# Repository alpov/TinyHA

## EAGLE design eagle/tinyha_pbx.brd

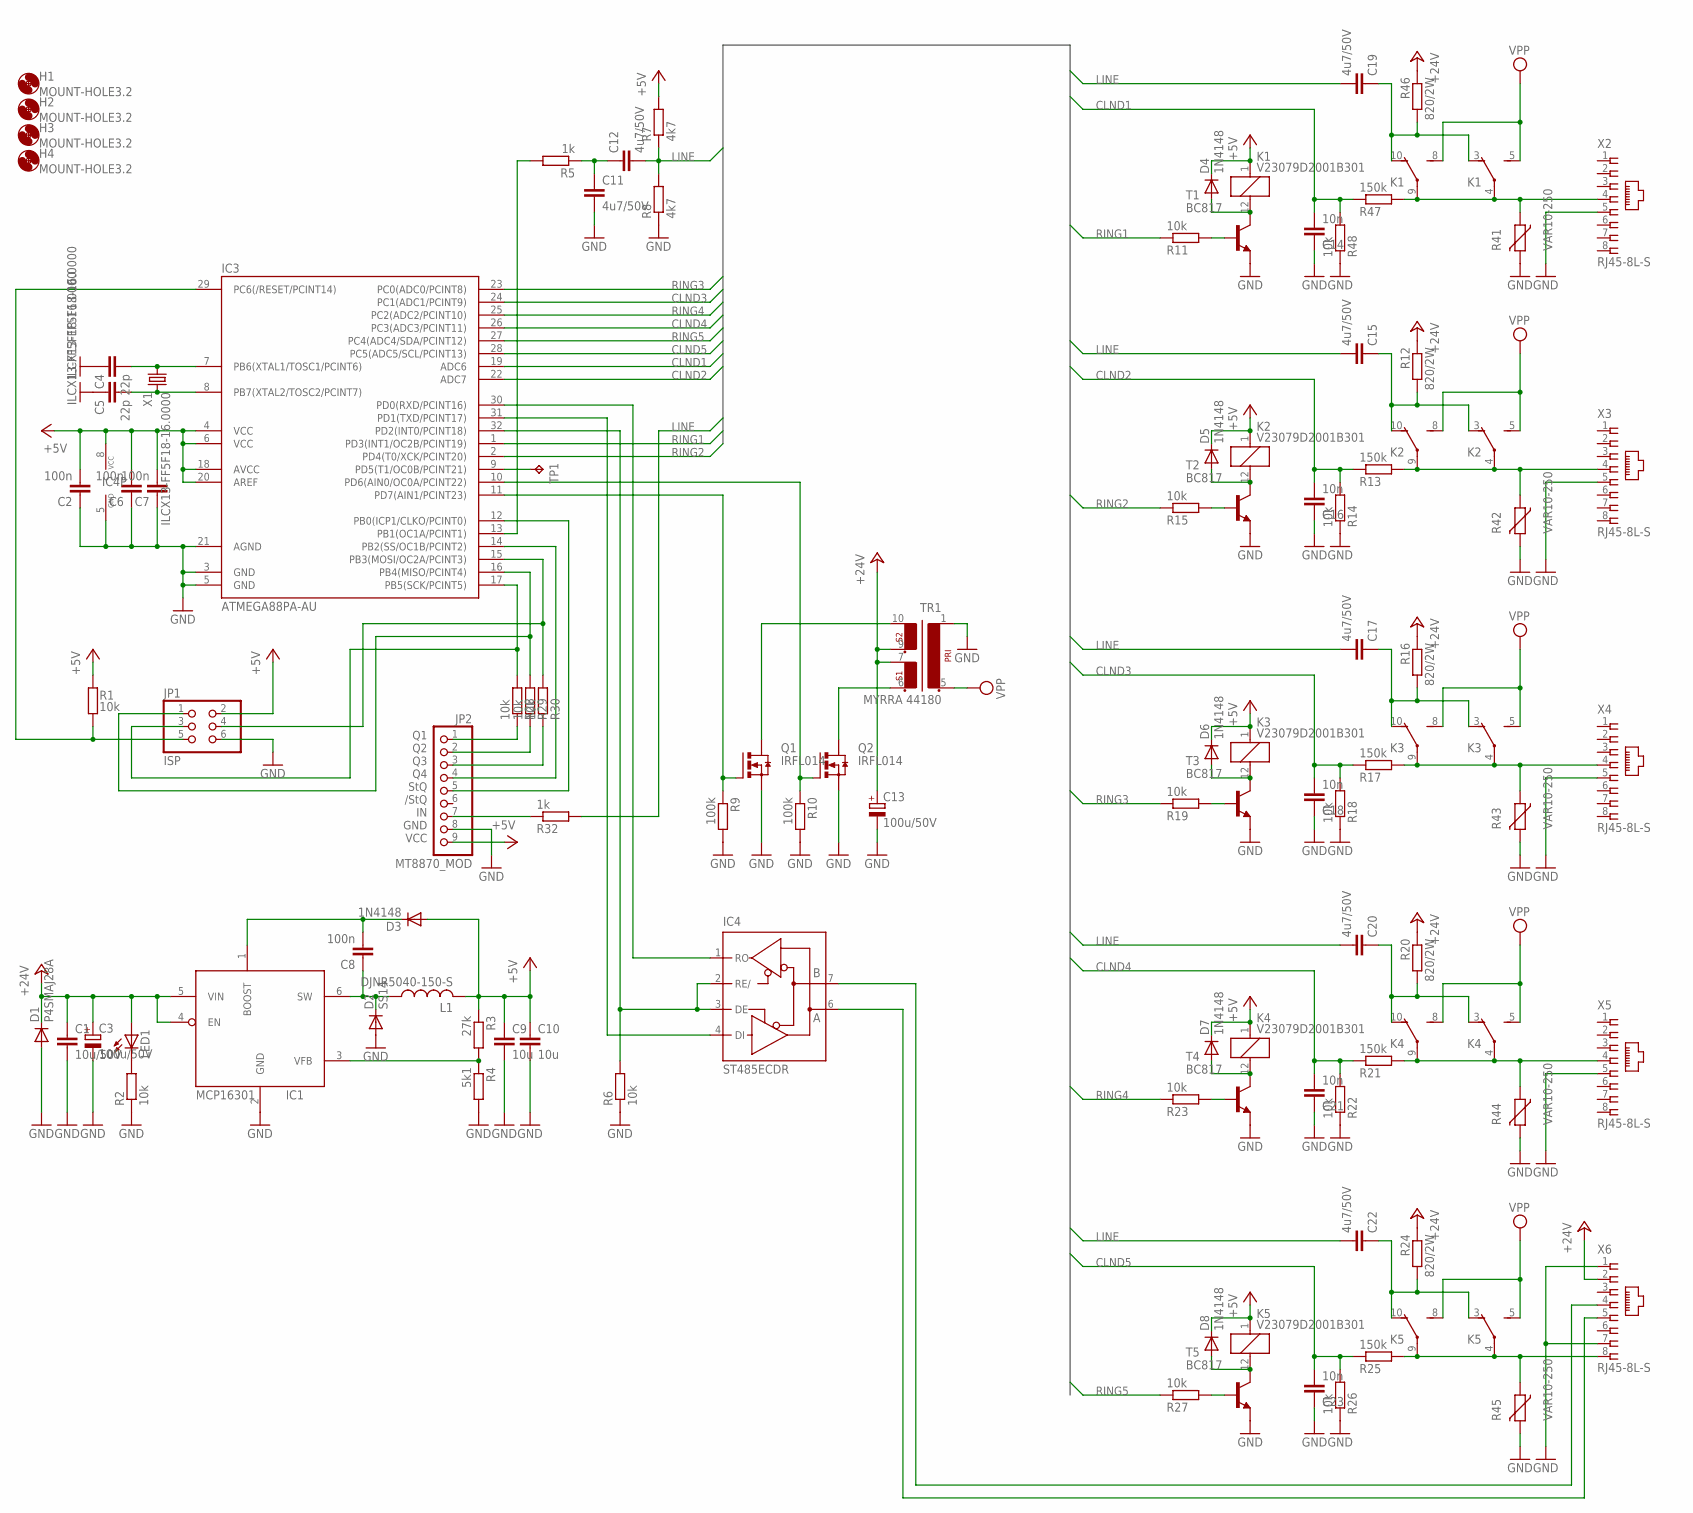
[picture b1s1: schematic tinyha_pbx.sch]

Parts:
C1: 10u/50V; C1210K
C2: 100n; C1206K
C3, C13: 100u/50V; E3,5-8
C4, C5: 22p; C0805K
C6, C7, C8: 100n; C0805K
C9, C10: 10u; C0805K
C11, C12, C15, C17, C19, C20, C22: 4u7/50V; C1206
C14, C16, C18, C21, C23: 10n; C1206
D1: P4SMAJ28A; DO214AC
D2: SS14; DO214AC
D3: 1N4148; MICROMELF-W
D4, D5, D6, D7, D8: 1N4148; MINIMELF
H1, H2, H3, H4: MOUNT-HOLE3.2; 3,2
IC1: MCP16301; SOT23-6L
IC3: ATMEGA88PA-AU; TQFP32-08
IC4: ST485ECDR; SO08
JP1: ISP; 2X03
JP2: MT8870_MOD; 1X09
K1, K2, K3, K4, K5: V23079D2001B301; V23079D
L1: DJNR5040-150-S; DJNR5040
LED1: LED3MM
Q1, Q2: IRFL014; SOT223
R1: 10k; R0805
R2, R6, R11, R14, R15, R18, R19, R22, R23, R26, R27, R28, R29, R30, R48: 10k; R1206
R3: 27k; R0805
R4: 5k1; R0805
R5, R32: 1k; R1206
R7, R8: 4k7; R1206
R9, R10: 100k; R1206
R12, R16, R20, R24, R46: 820/2W; 0411/15
R13, R17, R21, R25, R47: 150k; R1206
R41, R42, R43, R44, R45: VAR10-250; R-7,5
T1, T2, T3, T4, T5: BC817; SOT23-BEC
TP1: TPB2,54; B2,54
TR1: MYRRA 44180; EI30-2
X1: ILCX13-FF5F18-16.0000; SMD3225
X2, X3, X4, X5, X6: RJ45-8L-S; RJ45-NO-SHIELD

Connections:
+5V: C2.2, C6.2, C7.2, C9.1, C10.1, D3.A, D4.C, D5.C, D6.C, D7.C, D8.C, IC3.4 (VCC), IC3.6 (VCC), IC3.18 (AVCC), IC3.20 (AREF), IC4.8 (VCC), JP1.2, JP2.9, K1.1, K2.1, K3.1, K4.1, K5.1, L1.2, R1.1, R3.1, R7.2
+24V: C1.1, C3.+, C13.+, D1.C, IC1.4 (EN), IC1.5 (VIN), LED1.A, R12.1, R16.1, R20.1, R24.1, R46.1, TR1.7 (4), TR1.9 (5), X6.2
CLND1: C14.2, IC3.19 (ADC6), R47.1, R48.2
CLND2: C16.2, IC3.22 (ADC7), R13.1, R14.2
CLND3: C18.2, IC3.24 (PC1(ADC1/PCINT9)), R17.1, R18.2
CLND4: C21.2, IC3.26 (PC3(ADC3/PCINT11)), R21.1, R22.2
CLND5: C23.2, IC3.28 (PC5(ADC5/SCL/PCINT13)), R25.1, R26.2
DIR: IC3.32 (PD2(INT0/PCINT18)), IC4.2 (RE/), IC4.3 (DE), R6.2
GND: C1.2, C2.1, C3.-, C4.1, C5.1, C6.1, C7.1, C9.2, C10.2, C11.2, C13.-, C14.1, C16.1, C18.1, C21.1, C23.1, D1.A, D2.A, IC1.2 (GND), IC3.3 (GND), IC3.5 (GND), IC3.21 (AGND), IC4.5 (GND), JP1.6, JP2.8, Q1.3 (S), Q2.3 (S), R2.1, R4.2, R6.1, R8.1, R9.2, R10.2, R14.1, R18.1, R22.1, R26.1, R41.2, R42.2, R43.2, R44.2, R45.2, R48.1, T1.E, T2.E, T3.E, T4.E, T5.E, TR1.1, X1.2 (GND), X1.4 (GND), X2.5, X3.5, X4.5, X5.5, X6.1, X6.7
LINE: C12.2, C15.2, C17.2, C19.2, C20.2, C22.2, R7.1, R8.2, R32.2
MISO: IC3.16 (PB4(MISO/PCINT4)), JP1.1, R29.2
MOSI: IC3.15 (PB3(MOSI/OC2A/PCINT3)), JP1.4, R30.2
unnamed: D4.A, K1.12 (2), T1.C
unnamed: R11.2, T1.B
unnamed: JP2.1, R28.1
unnamed: C15.1, K2.3 (O), K2.10 (O), R12.2
unnamed: K3.4, K3.9, R17.2, R43.1, X4.4
unnamed: K5.4, K5.9, R25.2, R45.1, X6.8
unnamed: K2.4, K2.9, R13.2, R42.1, X3.4
unnamed: K4.4, K4.9, R21.2, R44.1, X5.4
unnamed: IC3.9 (PD5(T1/OC0B/PCINT21)), TP1.TP
unnamed: D5.A, K2.12 (2), T2.C
unnamed: R15.2, T2.B
unnamed: C17.1, K3.3 (O), K3.10 (O), R16.2
unnamed: JP2.7, R32.1
unnamed: D6.A, K3.12 (2), T3.C
unnamed: R19.2, T3.B
unnamed: C20.1, K4.3 (O), K4.10 (O), R20.2
unnamed: D7.A, K4.12 (2), T4.C
unnamed: LED1.K (C), R2.2
unnamed: R23.2, T4.B
unnamed: C22.1, K5.3 (O), K5.10 (O), R24.2
unnamed: D8.A, K5.12 (2), T5.C
unnamed: R27.2, T5.B
unnamed: IC3.12 (PB0(ICP1/CLKO/PCINT0)), JP2.5
unnamed: IC4.7 (B), X6.4
unnamed: JP2.2, R29.1
unnamed: IC4.6 (A), X6.5
unnamed: JP2.3, R30.1
unnamed: IC3.10 (PD6(AIN0/OC0A/PCINT22)), Q2.1 (G), R10.1
unnamed: C11.1, C12.1, R5.1
unnamed: IC3.11 (PD7(AIN1/PCINT23)), Q1.1 (G), R9.1
unnamed: Q2.2 (D), Q2.4 (D), TR1.6 (3)
unnamed: Q1.2 (D), Q1.4 (D), TR1.10 (6)
unnamed: C4.2, IC3.7 (PB6(XTAL1/TOSC1/PCINT6)), X1.1
unnamed: IC3.14 (PB2(SS/OC1B/PCINT2)), JP2.4
unnamed: IC1.3 (VFB), R3.2, R4.1
unnamed: C8.1, D2.C, IC1.6 (SW), L1.1
unnamed: C8.2, D3.C, IC1.1 (BOOST)
unnamed: C5.2, IC3.8 (PB7(XTAL2/TOSC2/PCINT7)), X1.3 (2)
unnamed: IC3.13 (PB1(OC1A/PCINT1)), R5.2
unnamed: K1.4, K1.9, R41.1, R47.2, X2.4
unnamed: C19.1, K1.3 (O), K1.10 (O), R46.2
RESET: IC3.29 (PC6(/RESET/PCINT14)), JP1.5, R1.2
RING1: IC3.1 (PD3(INT1/OC2B/PCINT19)), R11.1
RING2: IC3.2 (PD4(T0/XCK/PCINT20)), R15.1
RING3: IC3.23 (PC0(ADC0/PCINT8)), R19.1
RING4: IC3.25 (PC2(ADC2/PCINT10)), R23.1
RING5: IC3.27 (PC4(ADC4/SDA/PCINT12)), R27.1
RXD: IC3.30 (PD0(RXD/PCINT16)), IC4.1 (RO)
SCK: IC3.17 (PB5(SCK/PCINT5)), JP1.3, R28.2
TXD: IC3.31 (PD1(TXD/PCINT17)), IC4.4 (DI)
VPP: K1.5 (S), K1.8 (S), K2.5 (S), K2.8 (S), K3.5 (S), K3.8 (S), K4.5 (S), K4.8 (S), K5.5 (S), K5.8 (S), TR1.5 (2)

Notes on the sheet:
StQ
/StQ
GND
VCC

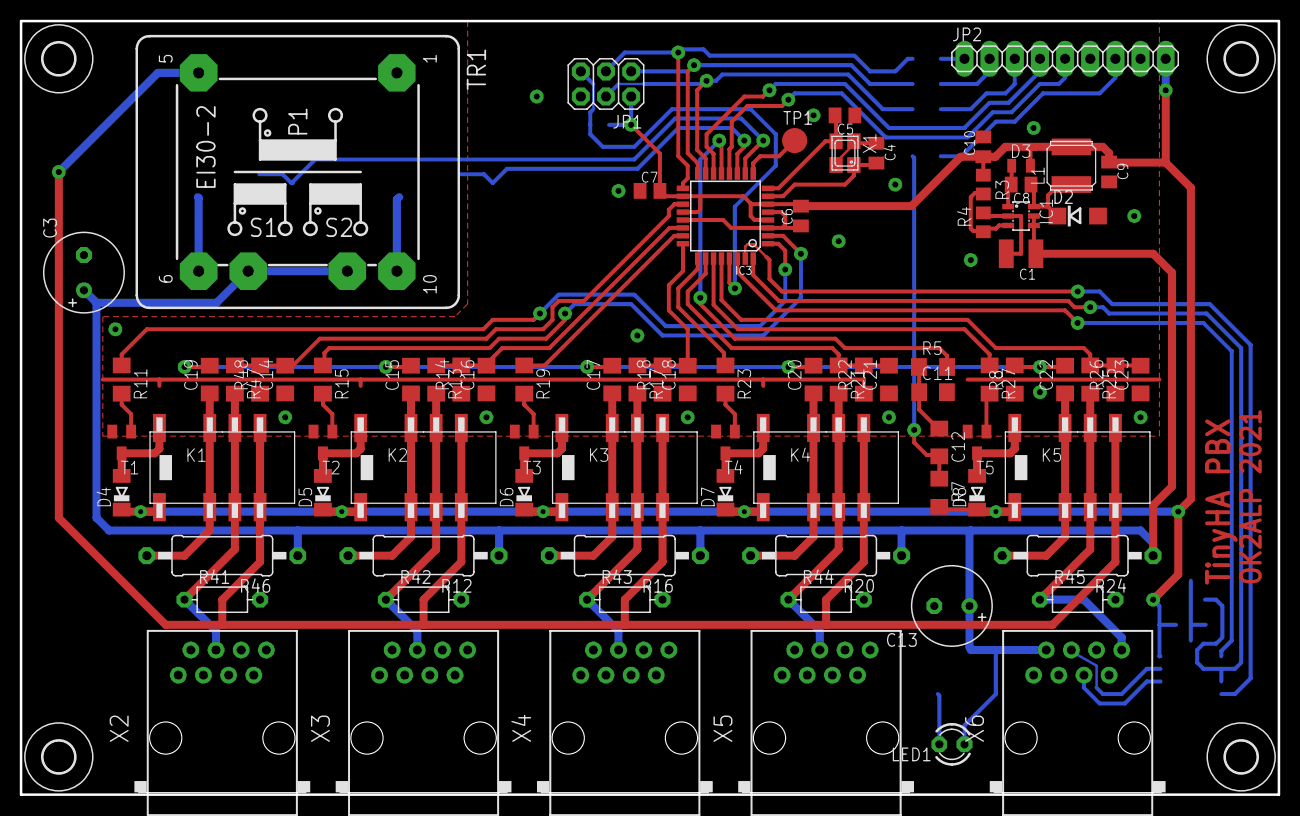
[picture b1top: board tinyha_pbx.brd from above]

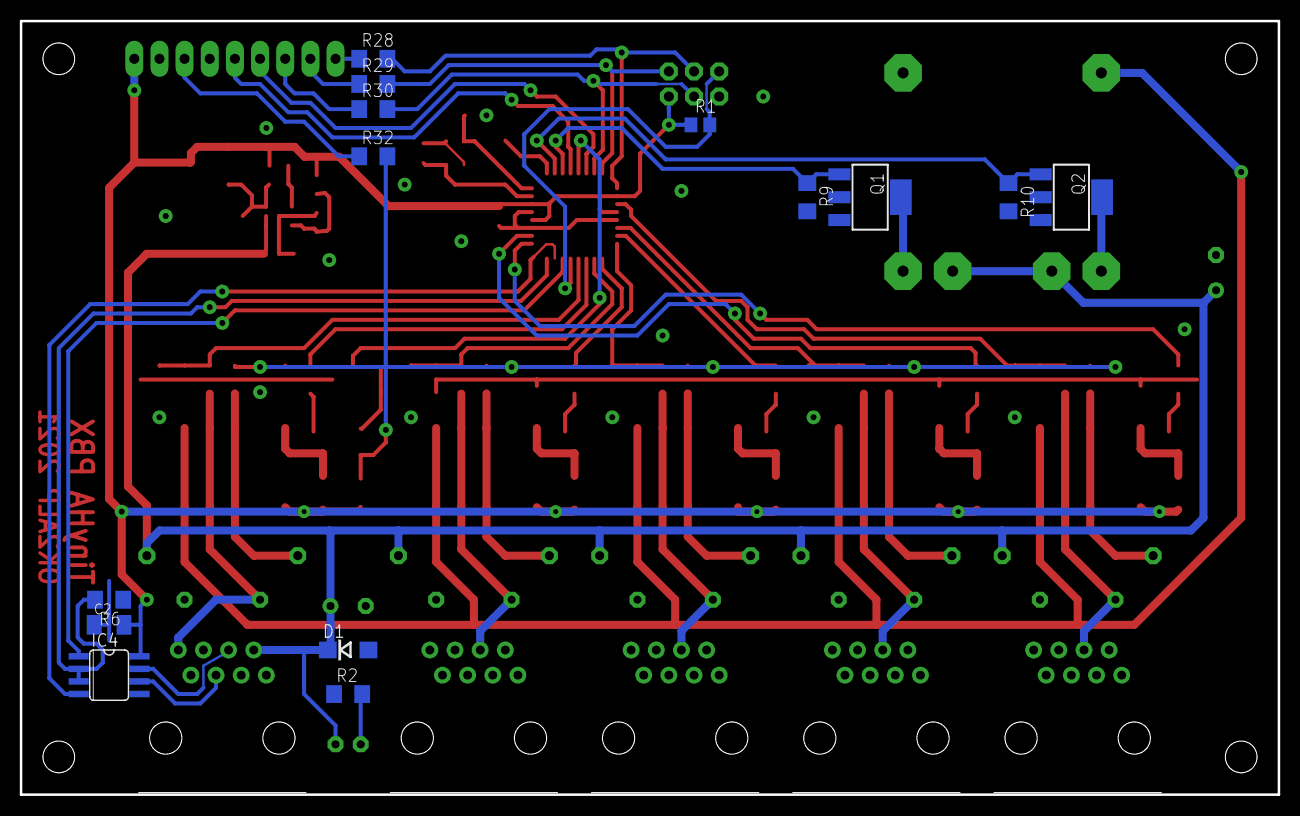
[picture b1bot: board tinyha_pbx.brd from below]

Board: 2 copper layers, 127.0 x 78.1 mm, 101 parts (14 on the bottom side), 63 nets.

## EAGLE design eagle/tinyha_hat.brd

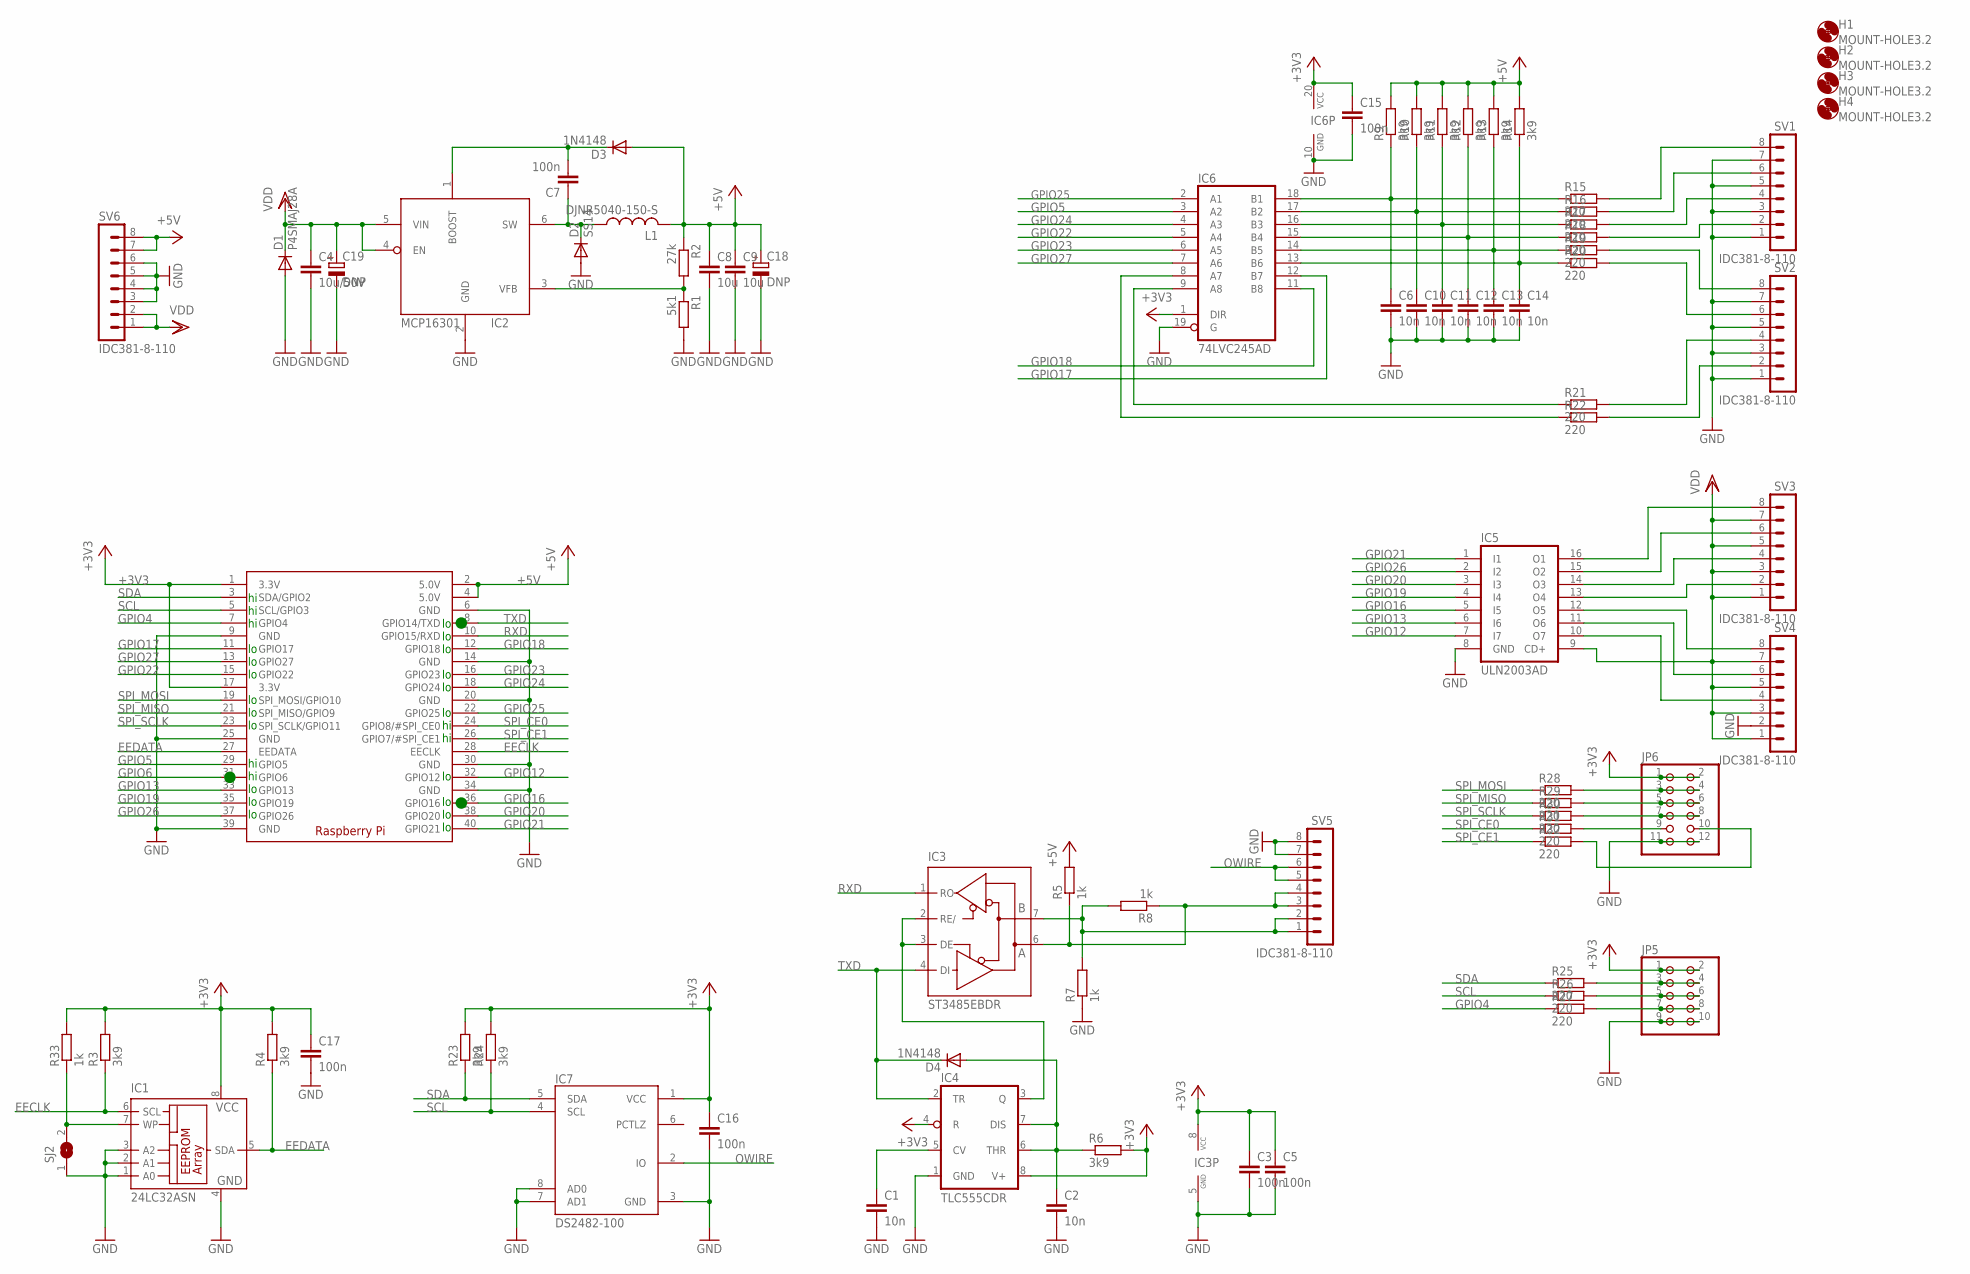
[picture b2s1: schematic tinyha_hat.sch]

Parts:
C1, C2, C6, C10, C11, C12, C13, C14: 10n; C0603K
C3, C5, C7, C15, C16, C17: 100n; C0603K
C4: 10u/50V; C1210K
C8, C9: 10u; C0805K
C18: DNP; E3,5-8
C19: DNP; E5-10,5
D1: P4SMAJ28A; DO214AC
D2: SS14; DO214AC
D3, D4: 1N4148; MICROMELF-W
H1, H2, H3, H4: MOUNT-HOLE3.2; 3,2
IC1: 24LC32ASN; SO-08
IC2: MCP16301; SOT23-6L
IC3: ST3485EBDR; SO08
IC4: TLC555CDR; SO08
IC5: ULN2003AD; SO16
IC6: 74LVC245AD; SO20W
IC7: DS2482-100; SOIC-8
JP5: PINHD-2X5; 2X05
JP6: PINHD-2X6; 2X06
L1: DJNR5040-150-S; DJNR5040
R1: 5k1; R0603
R2: 27k; R0603
R3, R4, R6, R9, R10, R11, R12, R13, R14, R23, R24: 3k9; R0603
R5, R7, R8, R33: 1k; R0603
R15, R16, R17, R18, R19, R20, R21, R22, R25, R26, R27, R28, R29, R30, R31, R32: 220; R0603
RPI1: RASPBERRYPI_BPLUS_ZERO; PI_HAT_ZERO
SJ2: SJ
SV1, SV2, SV3, SV4, SV5, SV6: IDC381-8-110; IDC381-8

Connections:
+3V3: C3.1, C5.1, C15.1, C16.1, C17.1, IC1.8 (VCC), IC3.8 (VCC), IC4.4 (R), IC4.8 (V+), IC6.1 (DIR), IC6.20 (VCC), IC7.1 (VCC), JP5.1, JP5.2, JP6.1, JP6.2, R3.2, R4.2, R6.2, R23.2, R24.2, R33.2, RPI1.1 (3.3V), RPI1.17 (3.3V)
+5V: C8.1, C9.1, C18.+, D3.A, L1.2, R2.1, R5.2, R9.2, R10.2, R11.2, R12.2, R13.2, R14.2, RPI1.2 (5.0V), RPI1.4 (5.0V), SV6.7, SV6.8
EECLK: IC1.6 (SCL), R3.1, RPI1.28 (EECLK)
EEDATA: IC1.5 (SDA), R4.1, RPI1.27 (EEDATA)
GND: C1.2, C2.2, C3.2, C4.2, C5.2, C6.2, C8.2, C9.2, C10.2, C11.2, C12.2, C13.2, C14.2, C15.2, C16.2, C17.2, C18.-, C19.-, D1.A, D2.A, IC1.1 (A0), IC1.2 (A1), IC1.3 (A2), IC1.4 (GND), IC2.2 (GND), IC3.5 (GND), IC4.1 (GND), IC5.8 (GND), IC6.10 (GND), IC6.19 (G), IC7.3 (GND), IC7.7 (AD1), IC7.8 (AD0), JP5.9, JP5.10, JP6.11, JP6.12, R1.2, R7.1, RPI1.6 (GND), RPI1.9 (GND), RPI1.14 (GND), RPI1.20 (GND), RPI1.25 (GND), RPI1.30 (GND), RPI1.34 (GND), RPI1.39 (GND), SJ2.1, SV1.1, SV1.3, SV1.5, SV1.7, SV2.1, SV2.3, SV2.5, SV2.7, SV4.2, SV5.7, SV5.8, SV6.3, SV6.4, SV6.5, SV6.6
GPIO4: R27.1, RPI1.7 (GPIO4)
GPIO5: IC6.3 (A2), RPI1.29 (GPIO5)
GPIO6: RPI1.31 (GPIO6)
GPIO12: IC5.7 (I7), RPI1.32 (GPIO12)
GPIO13: IC5.6 (I6), RPI1.33 (GPIO13)
GPIO16: IC5.5 (I5), RPI1.36 (GPIO16)
GPIO17: IC6.12 (B7), RPI1.11 (GPIO17)
GPIO18: IC6.11 (B8), RPI1.12 (GPIO18)
GPIO19: IC5.4 (I4), RPI1.35 (GPIO19)
GPIO20: IC5.3 (I3), RPI1.38 (GPIO20)
GPIO21: IC5.1 (I1), RPI1.40 (GPIO21)
GPIO22: IC6.5 (A4), RPI1.15 (GPIO22)
GPIO23: IC6.6 (A5), RPI1.16 (GPIO23)
GPIO24: IC6.4 (A3), RPI1.18 (GPIO24)
GPIO25: IC6.2 (A1), RPI1.22 (GPIO25)
GPIO26: IC5.2 (I2), RPI1.37 (GPIO26)
GPIO27: IC6.7 (A6), RPI1.13 (GPIO27)
unnamed: C1.1, IC4.5 (CV)
unnamed: IC5.16 (O1), SV3.8
unnamed: IC3.2 (RE/), IC3.3 (DE), IC4.3 (Q)
unnamed: C2.1, D4.A, IC4.6 (THR), IC4.7 (DIS), R6.1
unnamed: IC5.15 (O2), SV3.6
unnamed: IC5.14 (O3), SV3.4
unnamed: IC5.13 (O4), SV3.2
unnamed: IC5.12 (O5), SV4.8
unnamed: IC5.11 (O6), SV4.6
unnamed: IC3.7 (B), R7.2, R8.2, SV5.1, SV5.2
unnamed: IC5.10 (O7), SV4.4
unnamed: C6.1, IC6.18 (B1), R9.1, R15.1
unnamed: C10.1, IC6.17 (B2), R10.1, R16.1
unnamed: IC2.3 (VFB), R1.1, R2.2
unnamed: C11.1, IC6.16 (B3), R11.1, R17.1
unnamed: C12.1, IC6.15 (B4), R12.1, R18.1
unnamed: C13.1, IC6.14 (B5), R13.1, R19.1
unnamed: C14.1, IC6.13 (B6), R14.1, R20.1
unnamed: R15.2, SV1.8
unnamed: C7.1, D2.C, IC2.6 (SW), L1.1
unnamed: R16.2, SV1.6
unnamed: C7.2, D3.C, IC2.1 (BOOST)
unnamed: R17.2, SV1.4
unnamed: R18.2, SV1.2
unnamed: R19.2, SV2.8
unnamed: R20.2, SV2.6
unnamed: JP6.3, JP6.4, R28.2
unnamed: JP6.5, JP6.6, R29.2
unnamed: IC6.9 (A8), R21.1
unnamed: IC6.8 (A7), R22.1
unnamed: R21.2, SV2.4
unnamed: R22.2, SV2.2
unnamed: JP6.7, JP6.8, R30.2
unnamed: JP6.9, R31.2
unnamed: JP6.10, R32.2
unnamed: JP5.3, JP5.4, R25.2
unnamed: JP5.5, JP5.6, R26.2
unnamed: JP5.7, JP5.8, R27.2
unnamed: IC1.7 (WP), R33.1, SJ2.2
unnamed: IC3.6 (A), R5.1, R8.1, SV5.3, SV5.4
OWIRE: IC7.2 (IO), SV5.5, SV5.6
RXD: IC3.1 (RO), RPI1.10 (GPIO15/RXD)
SCL: IC7.4 (SCL), R24.1, R26.1, RPI1.5 (SCL/GPIO3)
SDA: IC7.5 (SDA), R23.1, R25.1, RPI1.3 (SDA/GPIO2)
SPI_CE0: R31.1, RPI1.24 (GPIO8/#SPI_CE0)
SPI_CE1: R32.1, RPI1.26 (GPIO7/#SPI_CE1)
SPI_MISO: R29.1, RPI1.21 (SPI_MISO/GPIO9)
SPI_MOSI: R28.1, RPI1.19 (SPI_MOSI/GPIO10)
SPI_SCLK: R30.1, RPI1.23 (SPI_SCLK/GPIO11)
TXD: D4.C, IC3.4 (DI), IC4.2 (TR), RPI1.8 (GPIO14/TXD)
VDD: C4.1, C19.+, D1.C, IC2.4 (EN), IC2.5 (VIN), IC5.9 (CD+), SV3.1, SV3.3, SV3.5, SV3.7, SV4.1, SV4.3, SV4.5, SV4.7, SV6.1, SV6.2

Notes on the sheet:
hi hi hi lo lo lo lo lo lo hi hi lo lo lo
lo lo lo lo lo lo hi hi lo lo lo lo

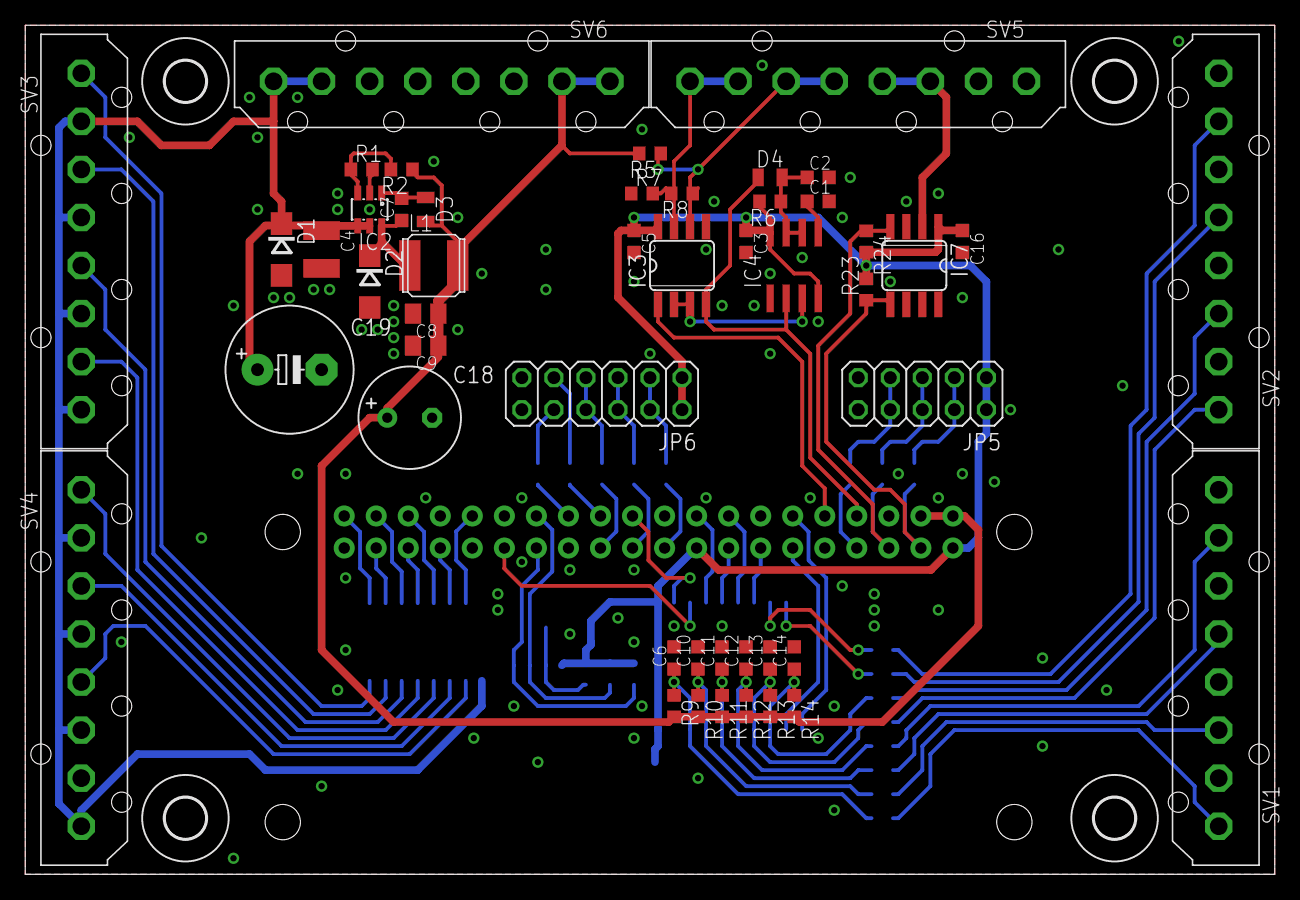
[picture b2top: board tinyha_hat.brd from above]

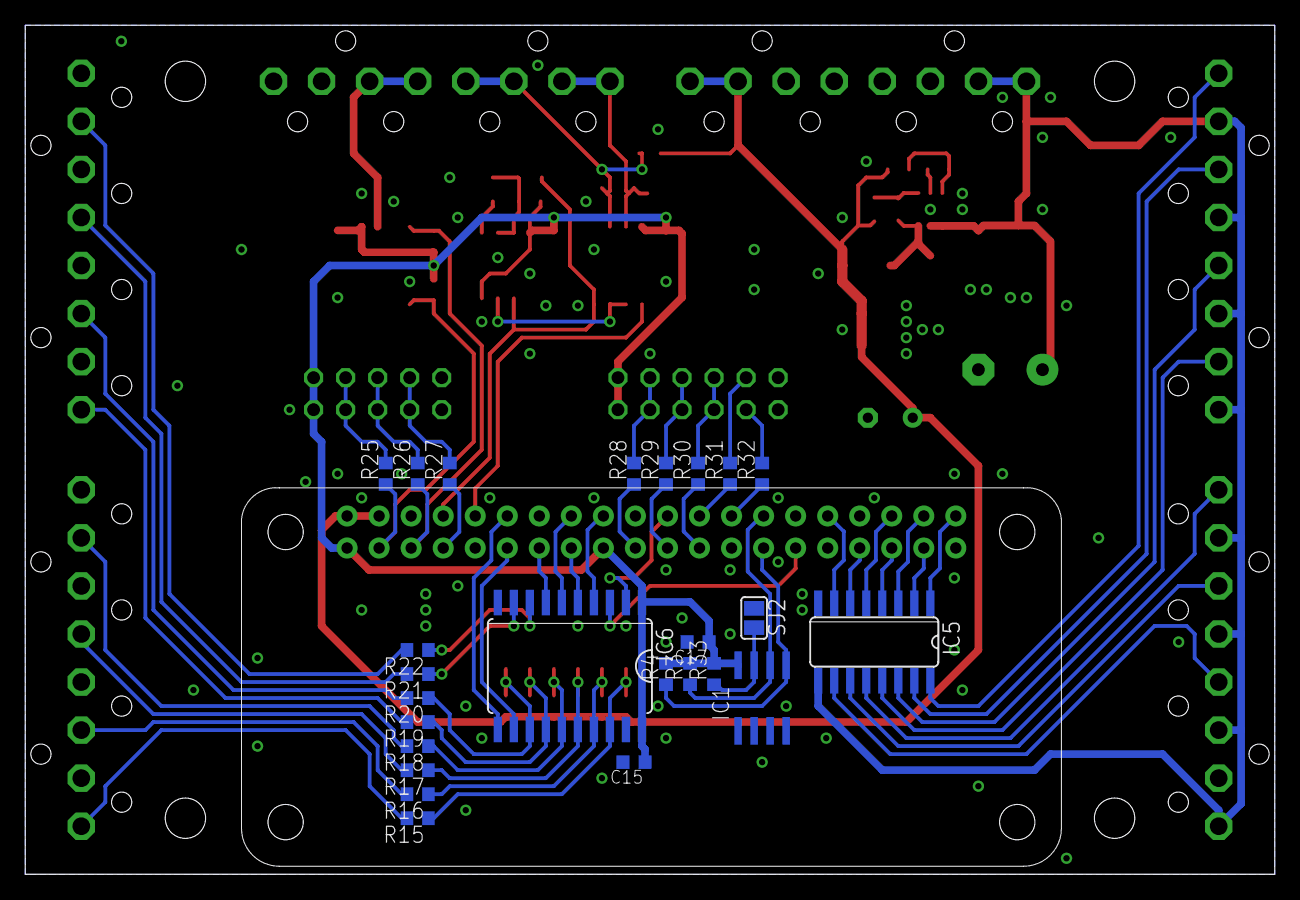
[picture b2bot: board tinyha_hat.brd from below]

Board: 2 copper layers, 99.1 x 67.3 mm, 78 parts (26 on the bottom side), 72 nets.

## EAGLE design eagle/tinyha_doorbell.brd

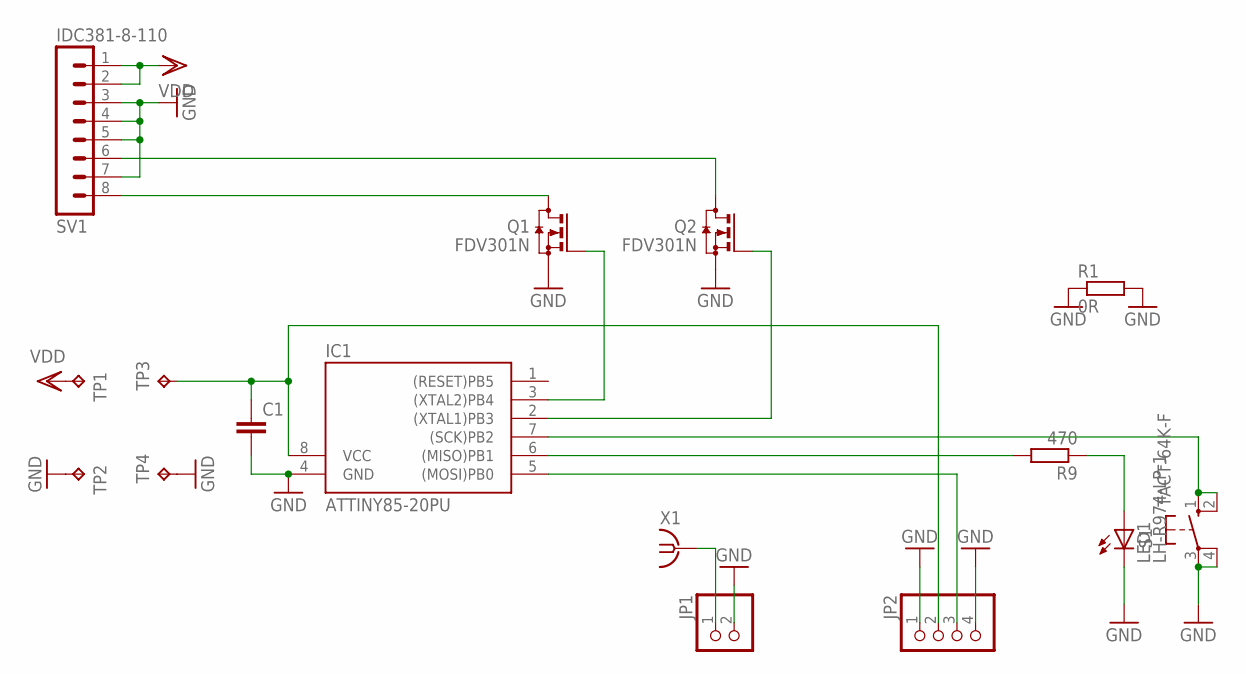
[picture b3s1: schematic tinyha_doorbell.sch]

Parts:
C1: C-EUC0805K; C0805K
IC1: ATTINY85-20PU; DIL08
JP1: PINHD-1X2; 1X02
JP2: PINHD-1X4; 1X04
LED1: LH-R974-LP-1; LED3MM
Q1, Q2: FDV301N; SOT23
R1: 0R; R1206
R9: 470; R0805
S1: TACT-64K-F; B3F-10XX
SV1: IDC381-8-110; IDC381-8
TP1, TP2, TP3, TP4: TPPAD1-13Y; P1-13Y
X1: SMA-DX-V; BU-SMA-V

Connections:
GND: C1.2, IC1.4 (GND), JP1.2, JP2.1, JP2.4, LED1.K (C), Q1.2 (S), Q2.2 (S), R1.1, R1.2, S1.3, S1.4 (P1), SV1.3, SV1.4, SV1.5, SV1.7, TP2.TP, TP4.TP, X1.2@1 (GND), X1.2@2 (GND), X1.2@3 (GND), X1.2@4 (GND)
unnamed: JP1.1, X1.1
unnamed: IC1.7 ((SCK)PB2), S1.1 (S), S1.2 (S1)
unnamed: IC1.5 ((MOSI)PB0), JP2.3
unnamed: IC1.6 ((MISO)PB1), R9.2
unnamed: IC1.3 ((XTAL2)PB4), Q1.1 (G)
unnamed: C1.1, IC1.8 (VCC), JP2.2, TP3.TP
unnamed: IC1.2 ((XTAL1)PB3), Q2.1 (G)
unnamed: Q2.3 (D), SV1.6
unnamed: Q1.3 (D), SV1.8
unnamed: LED1.A, R9.1
VDD: SV1.1, SV1.2, TP1.TP

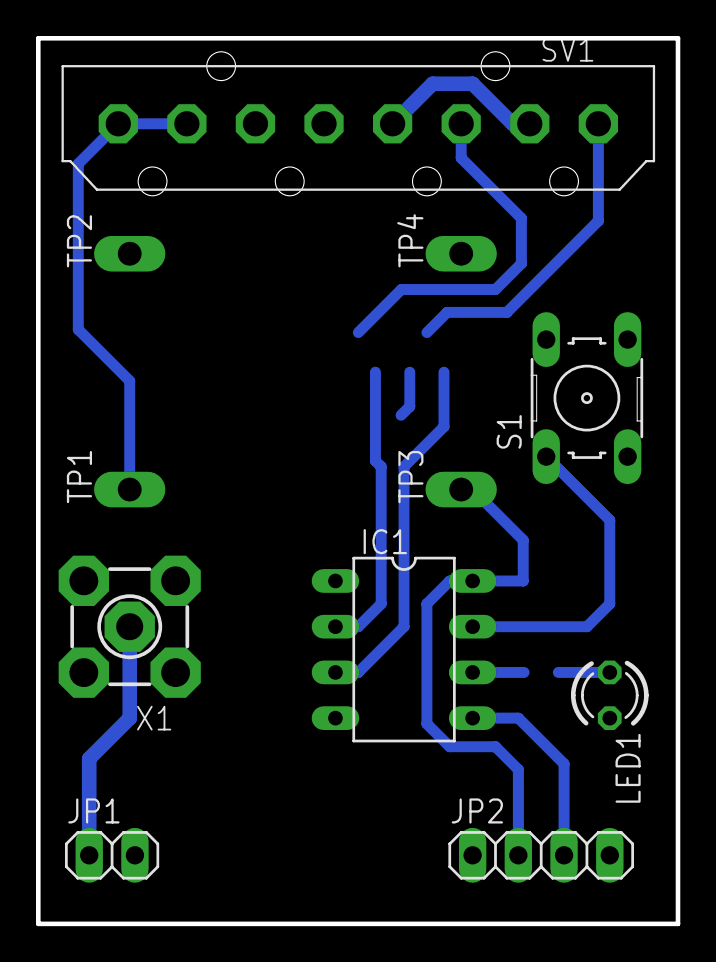
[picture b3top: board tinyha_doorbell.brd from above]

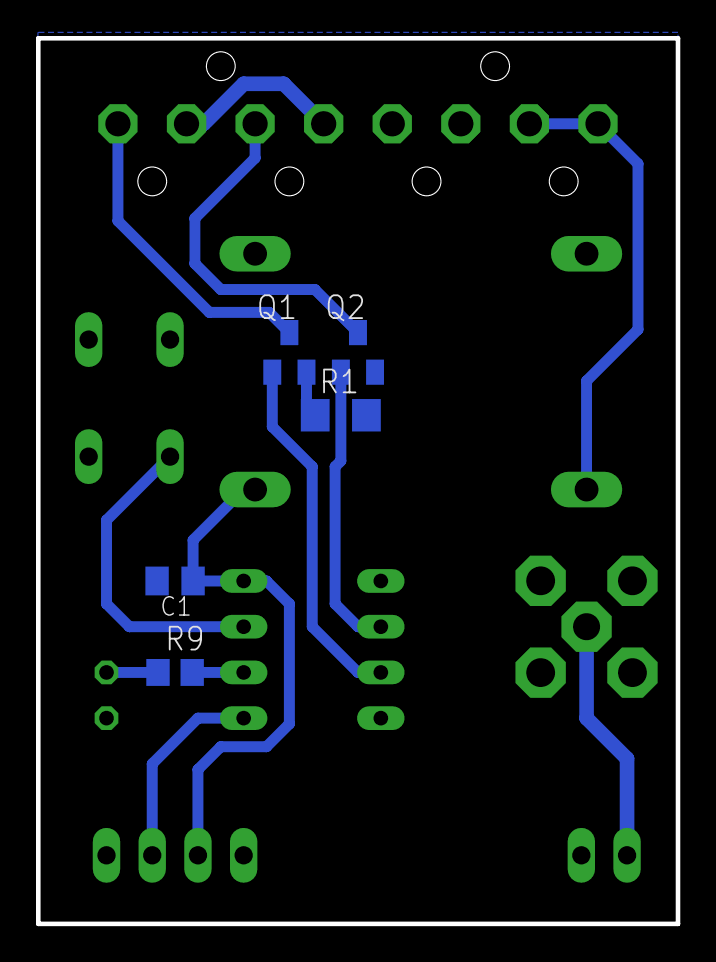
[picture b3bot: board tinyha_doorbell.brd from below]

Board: 2 copper layers, 35.5 x 49.2 mm, 16 parts (5 on the bottom side), 12 nets.

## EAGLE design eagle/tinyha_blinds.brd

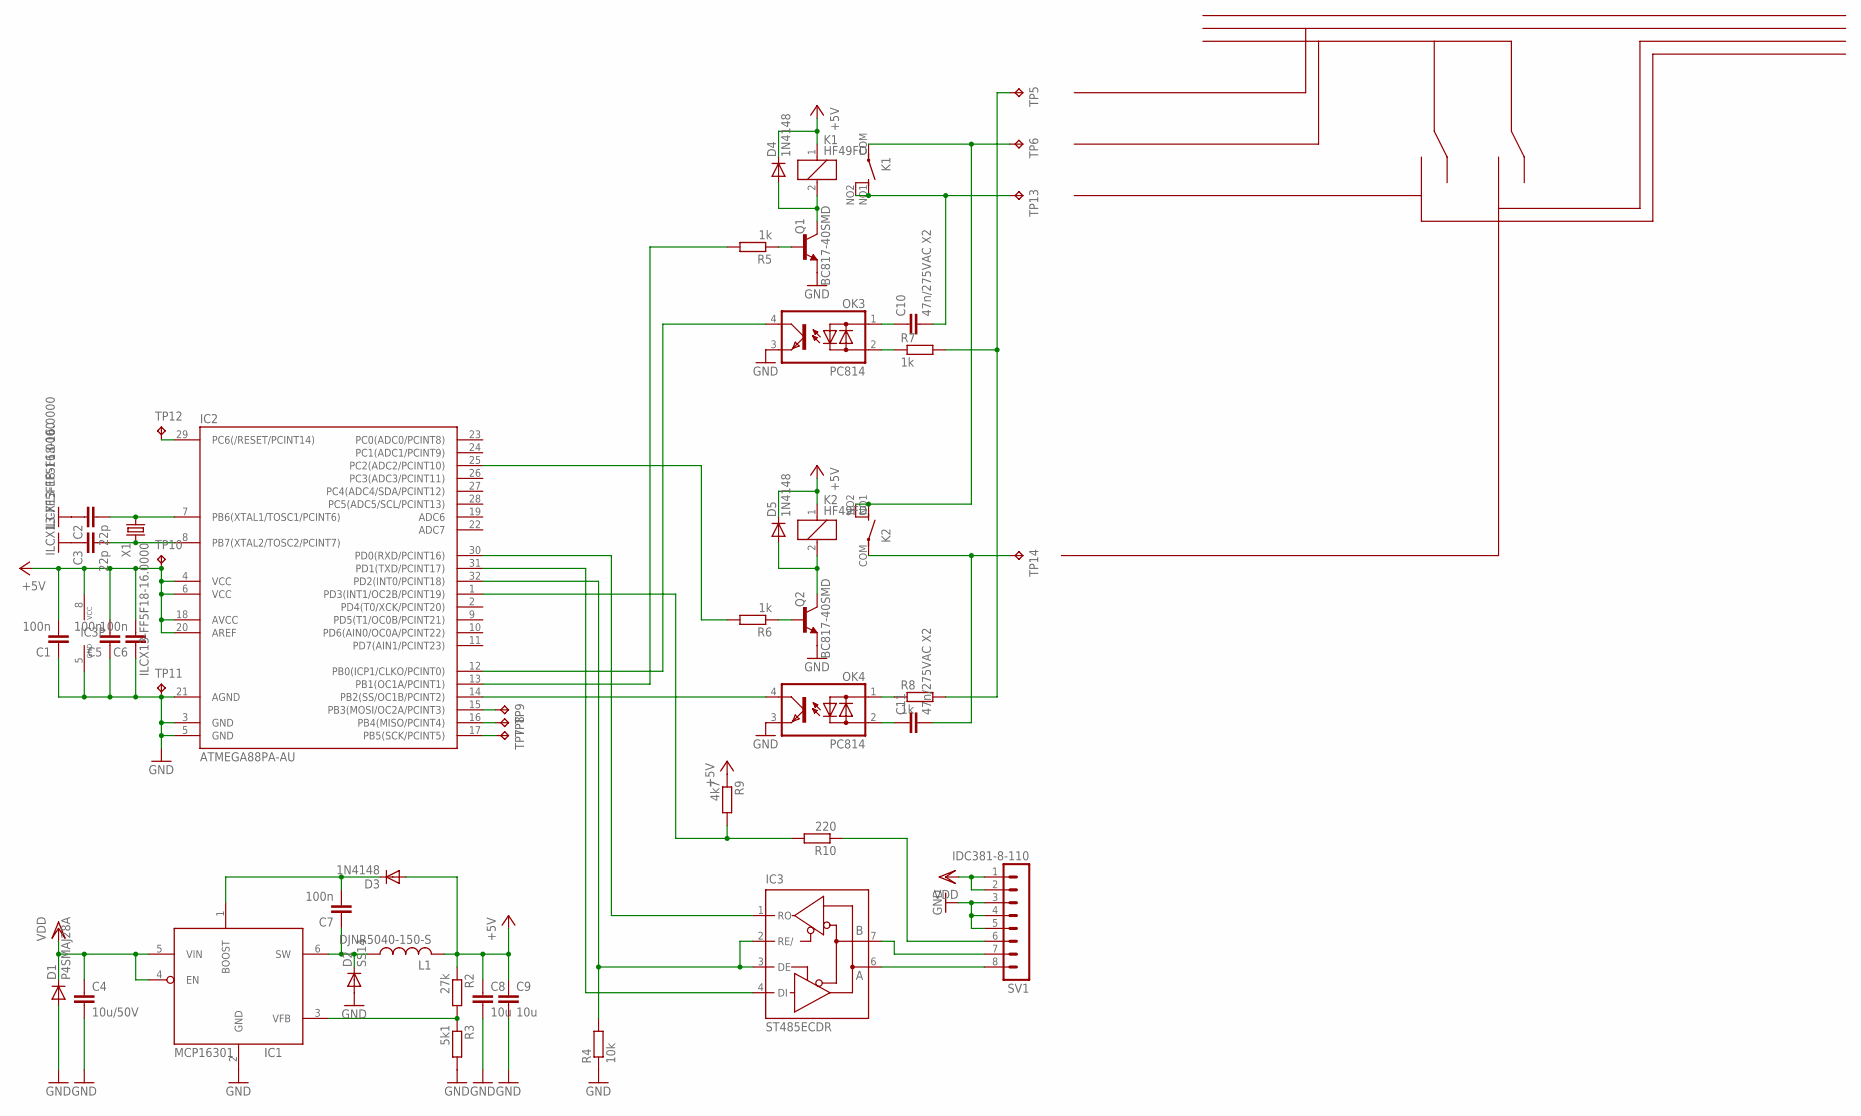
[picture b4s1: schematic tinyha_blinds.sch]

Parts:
C1, C5, C6, C7: 100n; C0603K
C2, C3: 22p; C0603K
C4: 10u/50V; C1210K
C8, C9: 10u; C0805K
C10, C11: 47n/275VAC X2; C10B5
D1: P4SMAJ28A; DO214AC
D2: SS14; DO214AC
D3, D4, D5: 1N4148; MICROMELF-W
IC1: MCP16301; SOT23-6L
IC2: ATMEGA88PA-AU; MLF32
IC3: ST485ECDR; SO08
K1, K2: HF49FD; HF49D
L1: DJNR5040-150-S; DJNR5040
OK3, OK4: PC814; DIL04
Q1, Q2: BC817-40SMD; SOT23-BEC
R2: 27k; R0603
R3: 5k1; R0603
R4: 10k; R0603
R5, R6: 1k; R0603
R7, R8: 1k; 0207/10
R9: 4k7; R0603
R10: 220; R0603
SV1: IDC381-8-110; IDC381-8
TP5, TP6, TP13, TP14: TP230; P1-20
TP7, TP8, TP9, TP10, TP11, TP12: TPB1,27; B1,27
X1: ILCX13-FF5F18-16.0000; SMD3225

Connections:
+5V: C1.2, C5.2, C6.2, C8.1, C9.1, D3.A, D4.C, D5.C, IC2.4 (VCC), IC2.6 (VCC), IC2.18 (AVCC), IC2.20 (AREF), IC3.8 (VCC), K1.1, K2.1, L1.2, R2.1, R9.1, TP10.TP
DIR: IC2.32 (PD2(INT0/PCINT18)), IC3.2 (RE/), IC3.3 (DE), R4.2
GND: C1.1, C2.1, C3.1, C4.2, C5.1, C6.1, C8.2, C9.2, D1.A, D2.A, IC1.2 (GND), IC2.3 (GND), IC2.5 (GND), IC2.21 (AGND), IC3.5 (GND), OK3.3 (E), OK4.3 (E), Q1.E, Q2.E, R3.2, R4.1, SV1.3, SV1.4, SV1.5, TP11.TP, X1.2 (GND), X1.4 (GND)
unnamed: R7.2, R8.2, TP5.TP
unnamed: C11.2, K2.COM, TP14.TP
unnamed: C10.2, K1.NO1 (S1), K1.NO2 (S2), TP13.TP
unnamed: Q2.B, R6.1
unnamed: Q1.B, R5.1
unnamed: IC2.13 (PB1(OC1A/PCINT1)), R5.2
unnamed: IC2.25 (PC2(ADC2/PCINT10)), R6.2
unnamed: IC2.29 (PC6(/RESET/PCINT14)), TP12.TP
unnamed: IC2.12 (PB0(ICP1/CLKO/PCINT0)), OK3.4 (C)
unnamed: IC3.7 (B), SV1.7
unnamed: D5.A, K2.2, Q2.C
unnamed: IC2.14 (PB2(SS/OC1B/PCINT2)), OK4.4 (C)
unnamed: OK4.1 (AC1), R8.1
unnamed: IC1.3 (VFB), R2.2, R3.1
unnamed: IC2.15 (PB3(MOSI/OC2A/PCINT3)), TP9.TP
unnamed: K1.COM, K2.NO1 (S1), K2.NO2 (S2), TP6.TP
unnamed: C11.1, OK4.2 (AC2)
unnamed: R10.1, SV1.6
unnamed: IC2.1 (PD3(INT1/OC2B/PCINT19)), R9.2, R10.2
unnamed: C7.1, D2.C, IC1.6 (SW), L1.1
unnamed: D4.A, K1.2, Q1.C
unnamed: C7.2, D3.C, IC1.1 (BOOST)
unnamed: IC3.6 (A), SV1.8
unnamed: C3.2, IC2.8 (PB7(XTAL2/TOSC2/PCINT7)), X1.3 (2)
unnamed: C2.2, IC2.7 (PB6(XTAL1/TOSC1/PCINT6)), X1.1
unnamed: C10.1, OK3.1 (AC1)
unnamed: OK3.2 (AC2), R7.1
RXD: IC2.30 (PD0(RXD/PCINT16)), IC3.1 (RO)
TXD: IC2.31 (PD1(TXD/PCINT17)), IC3.4 (DI)
UH: IC2.16 (PB4(MISO/PCINT4)), TP8.TP
VDD: C4.1, D1.C, IC1.4 (EN), IC1.5 (VIN), SV1.1, SV1.2
WH: IC2.17 (PB5(SCK/PCINT5)), TP7.TP
